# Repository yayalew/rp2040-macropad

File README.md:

# RP2040 9-Key Macropad

A custom 9-key programmable macropad designed around the Raspberry Pi RP2040.

The project is currently focused on hardware development. Firmware development
has not yet begun.

## Features

- Raspberry Pi RP2040 microcontroller
- 3×3 mechanical keyboard matrix
- Per-key diode isolation
- Per-key WS2812 RGB backlighting
- Two analog rotary potentiometers
- 2.0-inch SPI TFT display
- USB-C connectivity and power
- External QSPI flash
- BOOTSEL and hardware reset controls
- SWD debugging interface
- USB ESD protection
- 3.3 V onboard regulation

## Project Status

**Hardware:** In development  
**PCB Revision:** v0.1  
**Firmware:** In Progress
**Manufacturing:** 5 units in hand 

## Hardware

Designed in KiCad 10.

### System Architecture

USB-C
→ USB protection
→ RP2040

RP2040 interfaces with:
- 3×3 keyboard matrix
- WS2812 RGB LED chain
- SPI TFT display
- 2× analog potentiometers
- external QSPI flash
- SWD debug interface

## PCB

### Top

### Bottom

### 3D Renders

## Enclosure

## Firmware

Firmware has not yet been completed.

Planned functionality includes:

- USB HID keyboard support
- programmable key mappings
- RGB lighting effects
- volume control
- configurable secondary analog control
- display UI
- persistent configuration

Potential firmware platforms include the Pico SDK and QMK.

## Roadmap

- [x] System architecture
- [x] RP2040 schematic
- [x] Keyboard matrix
- [x] RGB backlighting circuitry
- [x] USB-C interface
- [x] TFT interface
- [x] SWD debugging interface
- [x] PCB layout
- [x] Design-rule review
- [ ] Firmware - IN DEVELOPMENT

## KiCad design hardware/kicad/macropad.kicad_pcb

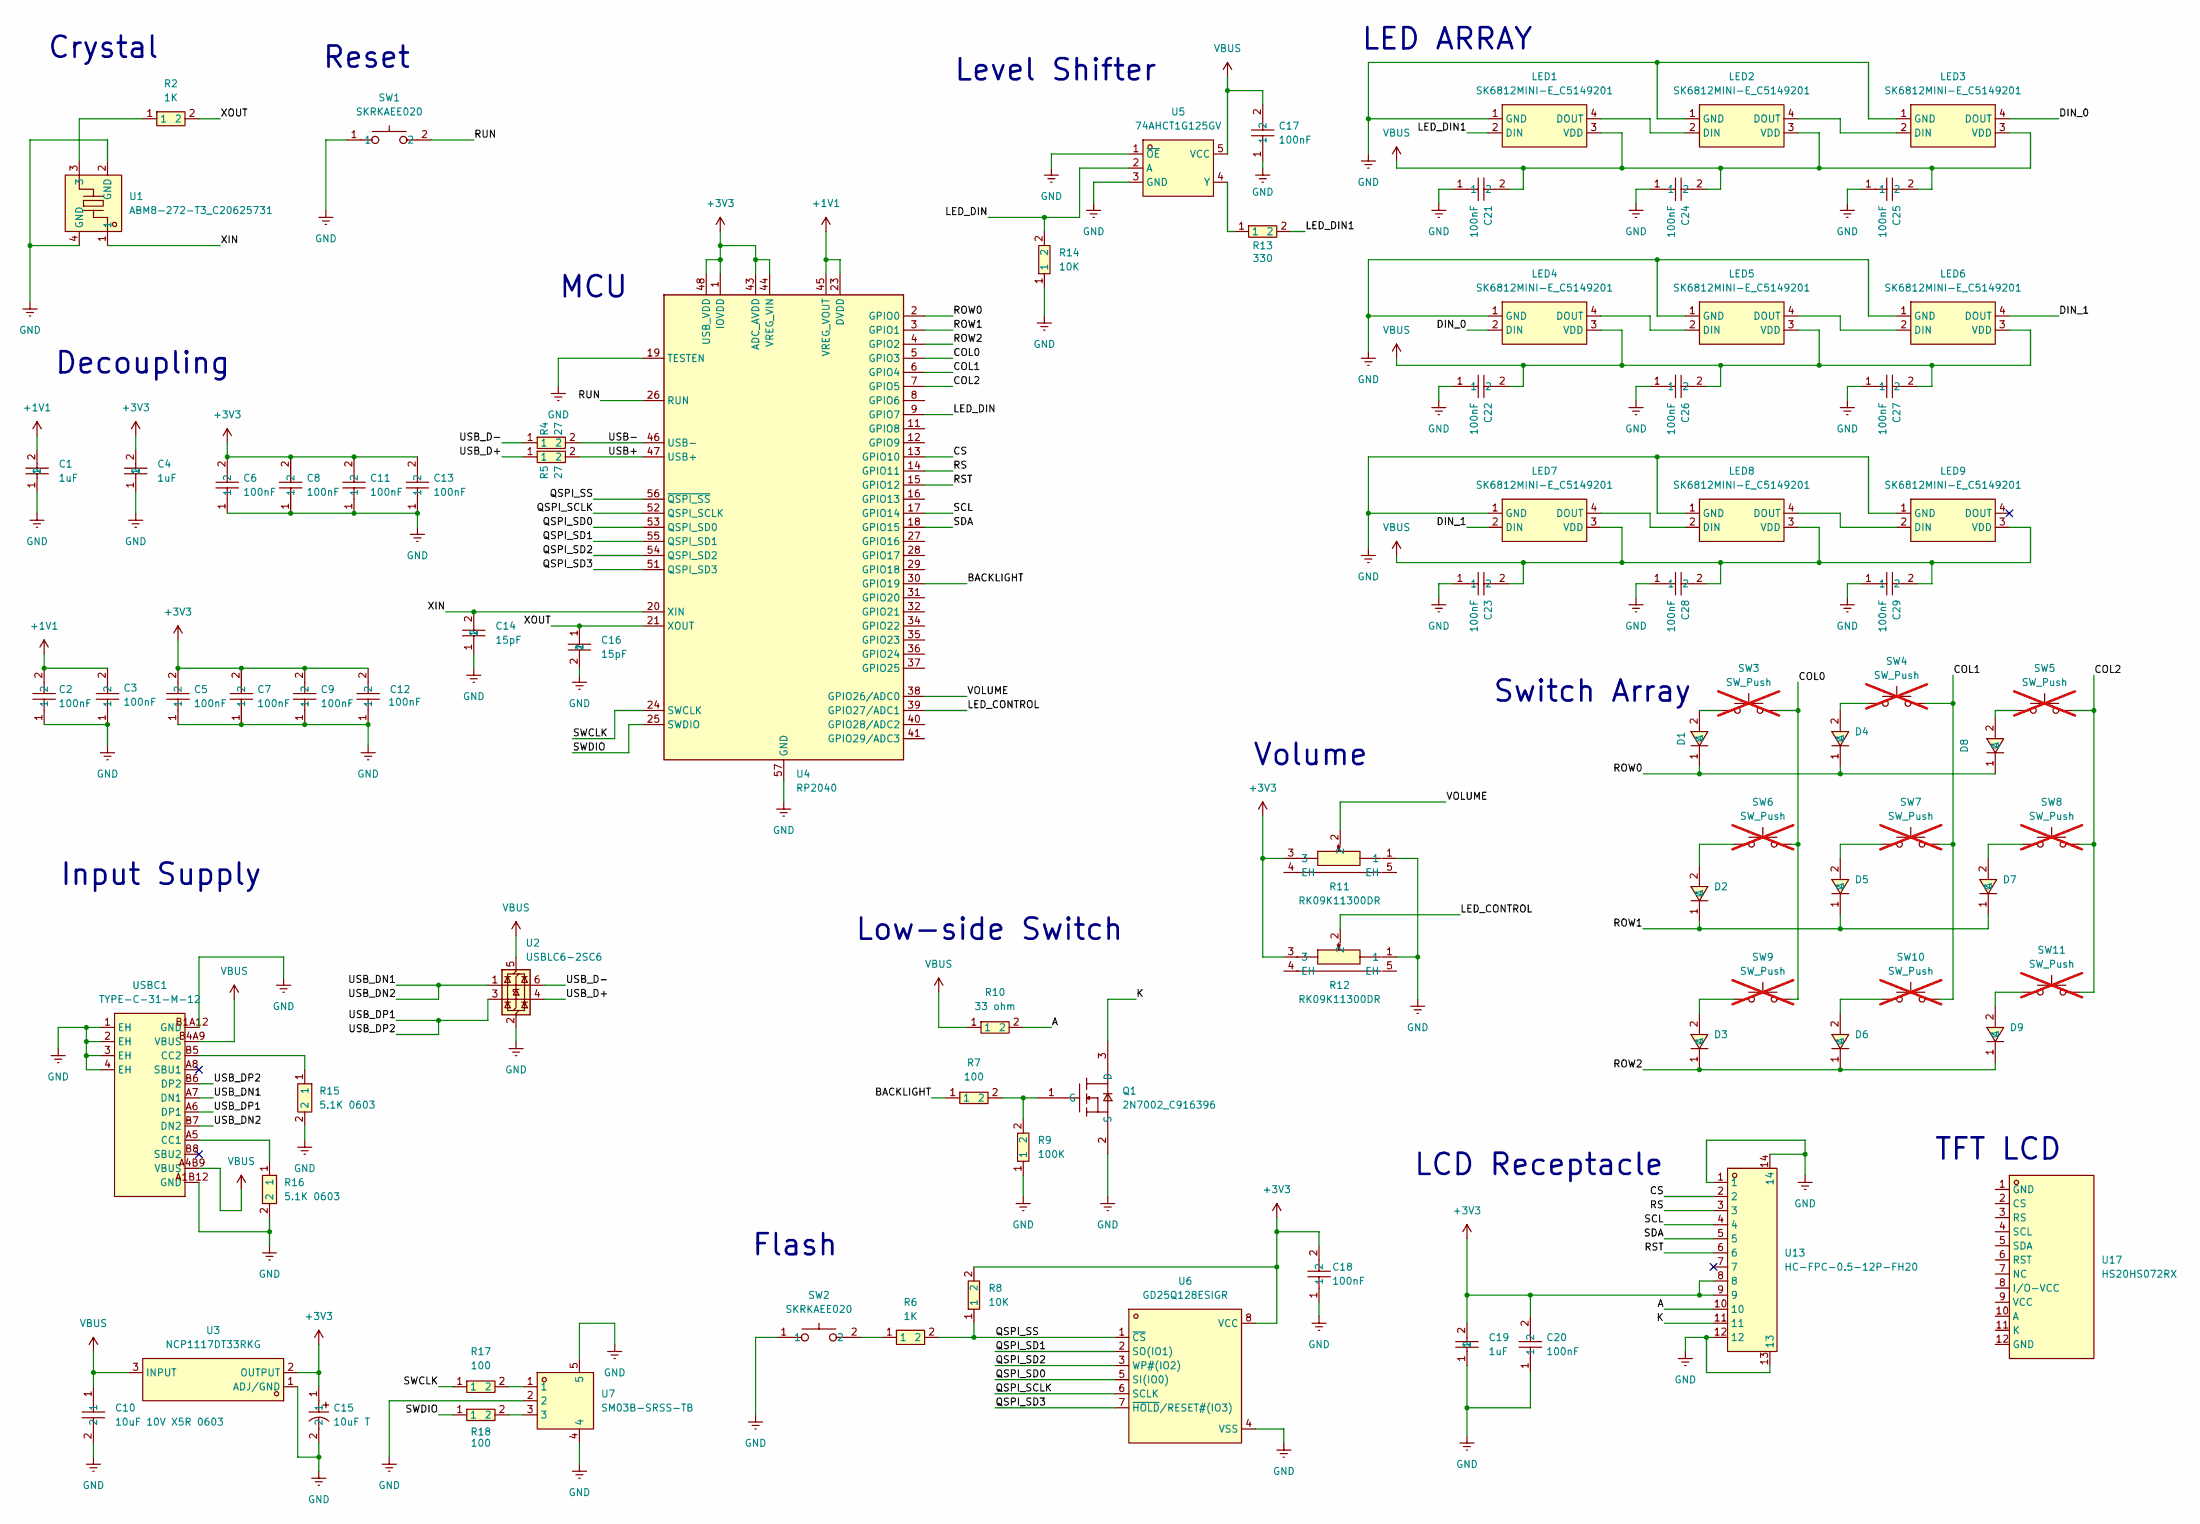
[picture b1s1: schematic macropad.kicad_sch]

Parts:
C1, C4, C19: 1uF; C0603; MPN CL10B105KA8NNNC; LCSC Part C29936
C2, C3, C5, C6, C7, C8, C9, C11, C12, C13, C17, C18, C20, C21, C22, C23, C24, C25, C26, C27, C28, C29: 100nF; C0603; Tolerance 10%; MPN 0603X7R104K250NT; LCSC Part C48579280
C10: 10uF 10V X5R 0603; C0603; MPN CL10A106KP8NNNC; LCSC Part C19702
C14, C16: 15pF; C0603; MPN CC0603JRNPO9BN150; LCSC Part C107037
C15: 10uF T; CAP-SMD_L2.0-W1.3-FD; MPN TMCP1A106MTRF; LCSC Part C1969735
D1, D2, D3, D4, D5, D6, D7, D8, D9: 1N4148W-7-F; SOD-123_L2.7-W1.6-LS3.7-RD-1; MPN 1N4148W-7-F; LCSC Part C83528
LED1, LED2, LED3, LED4, LED5, LED6, LED7, LED8, LED9: SK6812MINI-E_C5149201; LED-SMD_4P-L3.2-W2.8-LS5.9_SK6812MINI-E; MPN SK6812MINI-E; LCSC Part C5149201
Q1: 2N7002_C916396; SOT-23-3_L2.9-W1.3-P1.90-LS2.4-BR; MPN 2N7002; LCSC Part C916396
R2, R6: 1K; R0603; MPN FRC0603F1001TS; LCSC Part C2907002
R4, R5: 27; R0603; MPN 0603WAF270JT5E; LCSC Part C25190
R7, R17, R18: 100; R0603; MPN RCT03100RFLF; LCSC Part C177652
R8, R14: 10K; R0603; MPN RC0603FR-0710KL; LCSC Part C98220
R9: 100K; R0603; MPN RCT03100KFLF; LCSC Part C177608
R10: 33 ohm; R0805; MPN 0805W8F330JT5E; LCSC Part C17634
R11, R12: RK09K11300DR; RES-TH_RK09K113004U; MPN RK09K11300DR; LCSC Part C3020615
R13: 330; R0603; MPN RCT03330RJLF; LCSC Part C177341
R15, R16: 5.1K 0603; R0603; MPN FRC0603F5101TS; LCSC Part C2907044
SW1, SW2: SKRKAEE020; SW-SMD_L3.9-W3.0-P4.45; MPN SKRKAEE020; LCSC Part C115357
SW3, SW4, SW5, SW6, SW7, SW8, SW9, SW10, SW11: SW_Push; SW_Cherry_MX_PCB; LCSC Part C7519; not fitted
U1: ABM8-272-T3_C20625731; CRYSTAL-SMD_4P-L3.2-W2.5-BL; MPN ABM8-272-T3; LCSC Part C20625731
U2: USBLC6-2SC6; SOT-23-6
U3: NCP1117DT33RKG; TO-252-2_L6.6-W6.1-P4.57-LS9.9-TL-CW; MPN NCP1117DT33RKG; LCSC Part C88234
U4: RP2040; QFN-56-1EP_7x7mm_P0.4mm_EP3.2x3.2mm; LCSC Part C2040
U5: 74AHCT1G125GV; SOT-23-5_L3.0-W1.7-P0.95-LS2.8-BL; MPN 74AHCT1G125GV; LCSC Part C52140417
U6: GD25Q128ESIGR; SOP-8_L5.3-W5.3-P1.27-LS8.0-BL; MPN GD25Q128ESIGR; LCSC Part C2928891
U7: SM03B-SRSS-TB; CONN-SMD_SM03B-SRSS-TB-LF-SN-P; MPN SM03B-SRSS-TB(LF)(SN); LCSC Part C160403
U13: HC-FPC-0.5-12P-FH20; FPC-SMD_12P-P0.50_HC-FPC-0.5-12P-FH20; MPN HC-FPC-0.5-12P-FH20; LCSC Part C19273928
U17: HS20HS072RX; OLED-SMD_HS20HS072RX; MPN HS20HS072RX; LCSC Part C5329582
USBC1: TYPE-C-31-M-12; USB-C_SMD-TYPE-C-31-M-12_1; MPN TYPE-C-31-M-12; LCSC Part C165948

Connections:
+1V1: C1.2, C2.2, C3.2, U4.23 (DVDD), U4.45 (VREG_VOUT)
+3V3: C4.2, C5.2, C6.2, C7.2, C8.2, C9.2, C11.2, C12.2, C13.2, C15.1, C18.2, C19.2, C20.2, R8.2, R11.3, R12.3, U3.2 (OUTPUT), U4.1 (IOVDD), U4.10 (IOVDD), U4.22 (IOVDD), U4.33 (IOVDD), U4.42 (IOVDD), U4.43 (ADC_AVDD), U4.44 (VREG_VIN), U4.48 (USB_VDD), U4.49 (IOVDD), U6.8 (VCC), U13.8, U13.9
/A: R10.2, U13.10
/BACKLIGHT: R7.1, U4.30 (GPIO19)
/COL0: SW3.2, SW6.2, SW9.2, U4.5 (GPIO3)
/COL1: SW4.2, SW7.2, SW10.2, U4.6 (GPIO4)
/COL2: SW5.2, SW8.2, SW11.2, U4.7 (GPIO5)
/CS: U4.13 (GPIO10), U13.2
/DIN_0: LED3.4 (DOUT), LED4.2 (DIN)
/DIN_1: LED6.4 (DOUT), LED7.2 (DIN)
/K: Q1.3 (D), U13.11
/LED_CONTROL: R12.2, U4.39 (GPIO27/ADC1)
/LED_DIN: R14.2, U4.9 (GPIO7), U5.2 (A)
/LED_DIN1: LED1.2 (DIN), R13.2
/QSPI_SCLK: U4.52 (QSPI_SCLK), U6.6 (SCLK)
/QSPI_SD0: U4.53 (QSPI_SD0), U6.5 (SI(IO0))
/QSPI_SD1: U4.55 (QSPI_SD1), U6.2 (SO(IO1))
/QSPI_SD2: U4.54 (QSPI_SD2), U6.3 (WP#(IO2))
/QSPI_SD3: U4.51 (QSPI_SD3), U6.7 (~HOLD/RESET#(IO3))
/QSPI_SS: R6.2, R8.1, U4.56 (~QSPI_SS), U6.1 (~CS)
/ROW0: D1.1 (C), D4.1 (C), D8.1 (C), U4.2 (GPIO0)
/ROW1: D2.1 (C), D5.1 (C), D7.1 (C), U4.3 (GPIO1)
/ROW2: D3.1 (C), D6.1 (C), D9.1 (C), U4.4 (GPIO2)
/RS: U4.14 (GPIO11), U13.3
/RST: U4.15 (GPIO12), U13.6
/RUN: SW1.2, U4.26 (RUN)
/SCL: U4.17 (GPIO14), U13.4
/SDA: U4.18 (GPIO15), U13.5
/SWCLK: R17.1, U4.24 (SWCLK)
/SWDIO: R18.1, U4.25 (SWDIO)
/USB+: R5.2, U4.47 (USB+)
/USB-: R4.2, U4.46 (USB-)
/USB_D+: R5.1, U2.4 (I/O2)
/USB_D-: R4.1, U2.6 (I/O1)
/USB_DN1: U2.1 (I/O1), USBC1.A7 (DN1), USBC1.B7 (DN2)
/USB_DP1: U2.3 (I/O2), USBC1.A6 (DP1), USBC1.B6 (DP2)
/VOLUME: R11.2, U4.38 (GPIO26/ADC0)
/XIN: C14.2, U1.1, U4.20 (XIN)
/XOUT: C16.1, R2.2, U4.21 (XOUT)
GND: C1.1, C2.1, C3.1, C4.1, C5.1, C6.1, C7.1, C8.1, C9.1, C10.2, C11.1, C12.1, C13.1, C14.1, C15.2, C16.2, C17.1, C18.1, C19.1, C20.1, C21.1, C22.1, C23.1, C24.1, C25.1, C26.1, C27.1, C28.1, C29.1, LED1.1 (GND), LED2.1 (GND), LED3.1 (GND), LED4.1 (GND), LED5.1 (GND), LED6.1 (GND), LED7.1 (GND), LED8.1 (GND), LED9.1 (GND), Q1.2 (S), R9.1, R11.1, R12.1, R14.1, R15.2, R16.2, SW1.1, SW2.1, U1.2 (GND), U1.4 (GND), U2.2 (GND), U3.1 (ADJ/GND), U4.19 (TESTEN), U4.57 (GND), U5.1 (~OE), U5.3 (GND), U6.4 (VSS), U7.2, U7.4, U7.5, U13.1, U13.12, U13.13, U13.14, USBC1.1 (EH), USBC1.2 (EH), USBC1.3 (EH), USBC1.4 (EH), USBC1.A1B12 (GND), USBC1.B1A12 (GND)
unnamed: D1.2 (A), SW3.1
unnamed: D2.2 (A), SW6.1
unnamed: D3.2 (A), SW9.1
unnamed: D4.2 (A), SW4.1
unnamed: D5.2 (A), SW7.1
unnamed: D6.2 (A), SW10.1
unnamed: D7.2 (A), SW8.1
unnamed: D8.2 (A), SW5.1
unnamed: D9.2 (A), SW11.1
unnamed: LED1.4 (DOUT), LED2.2 (DIN)
unnamed: LED2.4 (DOUT), LED3.2 (DIN)
unnamed: LED4.4 (DOUT), LED5.2 (DIN)
unnamed: LED5.4 (DOUT), LED6.2 (DIN)
unnamed: LED7.4 (DOUT), LED8.2 (DIN)
unnamed: LED8.4 (DOUT), LED9.2 (DIN)
unnamed: Q1.1 (G), R7.2, R9.2
unnamed: R2.1, U1.3
unnamed: R6.1, SW2.2
unnamed: R17.2, U7.1
unnamed: R18.2, U7.3
unnamed: R13.1, U5.4 (Y)
unnamed: R16.1, USBC1.A5 (CC1)
unnamed: R15.1, USBC1.B5 (CC2)
VBUS: C10.1, C17.2, C21.2, C22.2, C23.2, C24.2, C25.2, C26.2, C27.2, C28.2, C29.2, LED1.3 (VDD), LED2.3 (VDD), LED3.3 (VDD), LED4.3 (VDD), LED5.3 (VDD), LED6.3 (VDD), LED7.3 (VDD), LED8.3 (VDD), LED9.3 (VDD), R10.1, U2.5 (VBUS), U3.3 (INPUT), U5.5 (VCC), USBC1.A4B9 (VBUS), USBC1.B4A9 (VBUS)

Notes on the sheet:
Input Supply
Reset
Low-side Switch
Level Shifter
LED ARRAY
Crystal
TFT LCD
LCD Receptacle
Decoupling
MCU
Switch Array
Flash
Volume

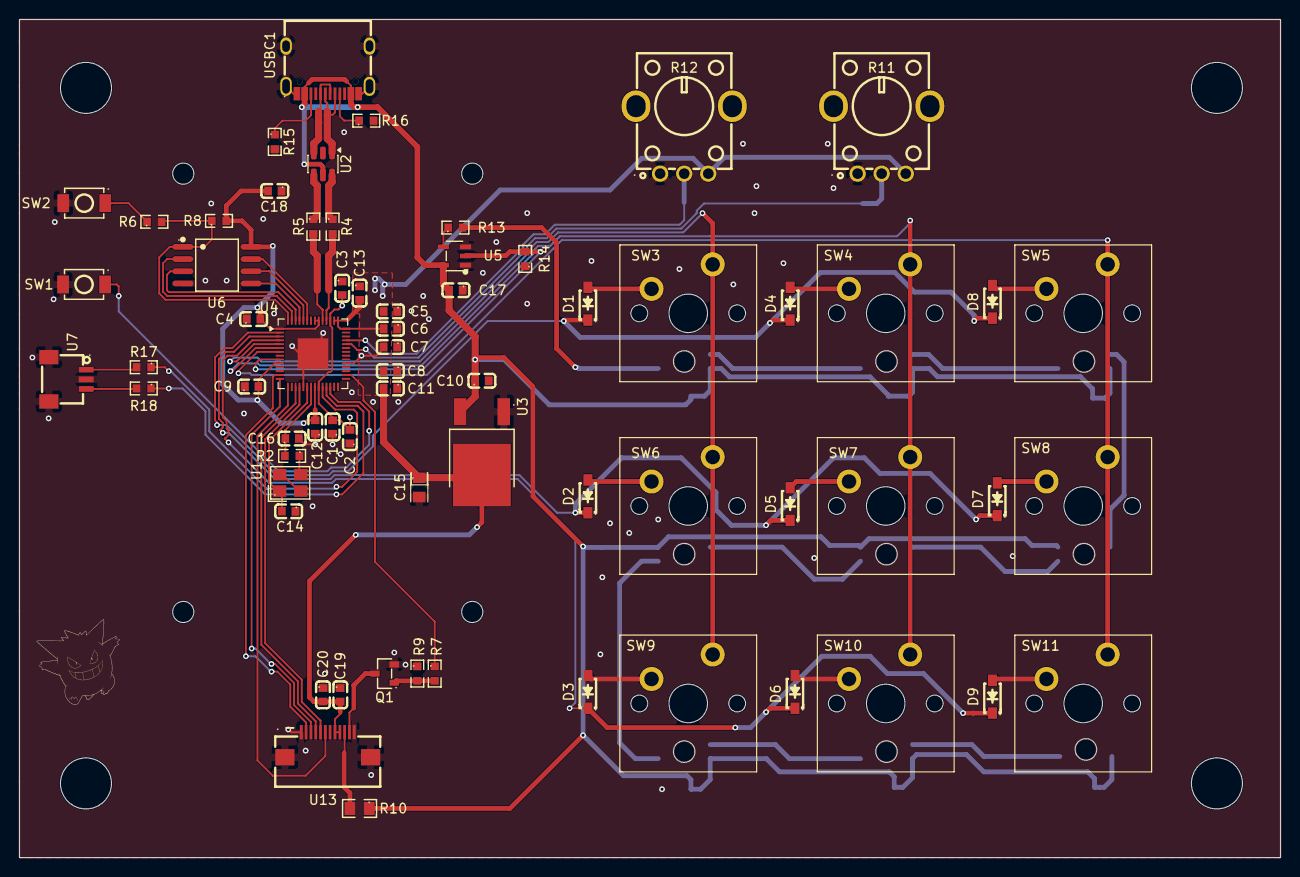
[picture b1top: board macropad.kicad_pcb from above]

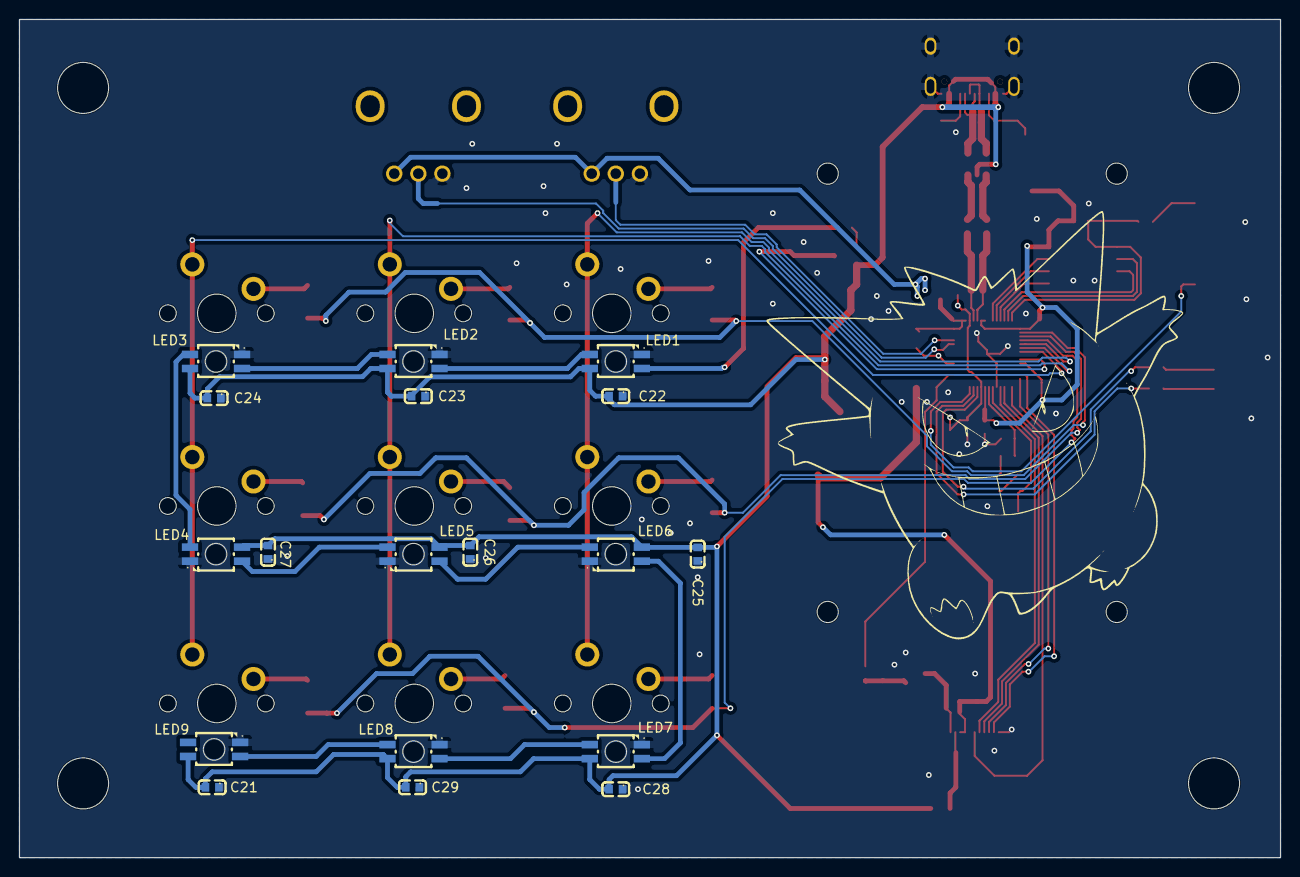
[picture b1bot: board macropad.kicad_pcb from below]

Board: 2 copper layers, 130.9 x 87.0 mm, 85 parts (19 on the bottom side), 64 nets.

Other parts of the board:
L111: LOGO
